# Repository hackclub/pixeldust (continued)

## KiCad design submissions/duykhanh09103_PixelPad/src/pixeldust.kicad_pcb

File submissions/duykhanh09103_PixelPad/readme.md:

---
name: "Khanh Duy Thanh Vo (my actually name in like gov document is Vo Thanh Khanh Duy because of last name fist name)"
slack_id: "U081GA0TAPR"
github_handle: "@duykhanh09103"
tutorial: none
wokwi: https://wokwi.com/projects/428194723515552769
---

# PixelPad

Replace the wokwi link below with yours

Wokwi link: https://wokwi.com/projects/428194723515552769

<!-- Uncomment the line below if you need a soldering iron -->
<!-- ⚠️ I would like to [reason for iron], so I would need a soldering iron. -->

<!-- Example: -->

| Comment           | Footprint                                      | Quantity | LCSC     | Cost   |
|-------------------|------------------------------------------------|----------|----------|--------|
| 100nF             | CL10B224KA8NNNC                                | 1        | C21120   | 0.0682$|
| WS2812B           | SK6812MINI-EA                                  | 9        | C5378731 |        |
| XIAO-RP2040-DIP   | XIAO-RP2040-DIP                                | 1        |          |        |
| Cherry MX         | SW_Cherry_MX_1.00u_PCB                         | 3        |          | 1.3$ for 3 |
| Hall Effect Sensor| GH39FKSW                                       | 3        | C266230  | $0.1439|

Tell us a little bit about your design process. What were some challenges? What helped?

originally i wanna design like  a 10x10 pixel board so i can display like image,qr,.. on it but i shuddenly have some idea about making  a keypad!
there was not a lot of challenge cuz @tobycm helped me a lot with kicad!(hes the goat 🗣). 

Some images of your design (make sure to include both the PCB and Schematic!):

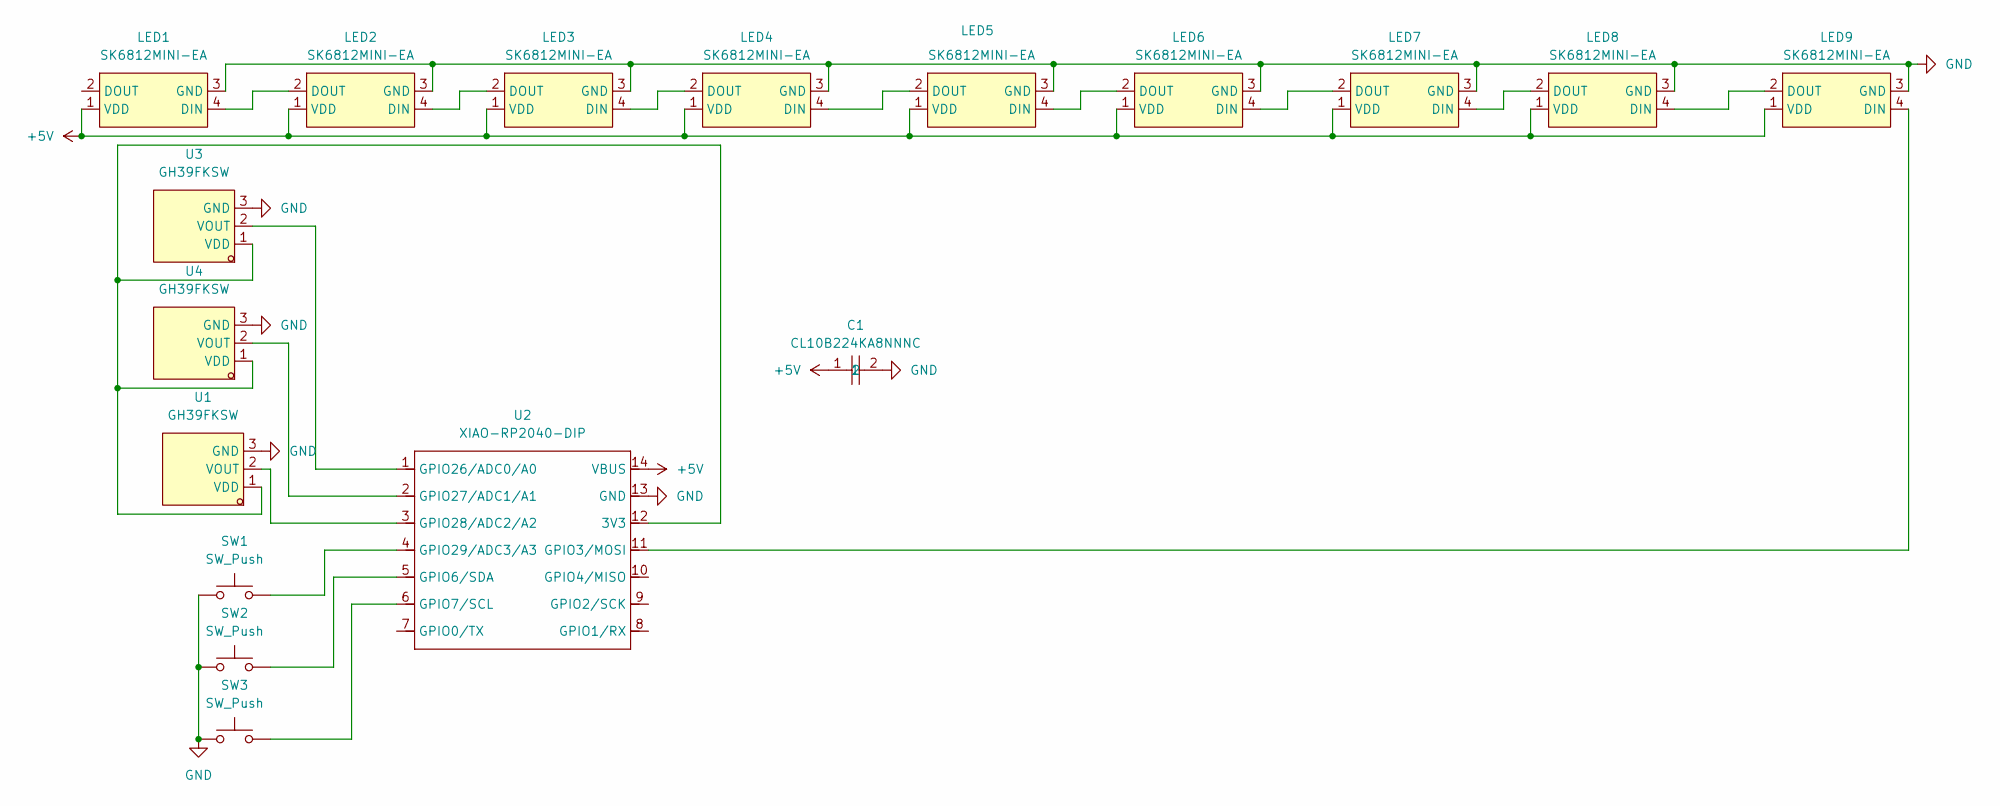
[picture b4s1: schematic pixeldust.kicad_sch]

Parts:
C1: CL10B224KA8NNNC; C0603; LCSC Part C21120
LED1, LED2, LED3, LED4, LED5, LED6, LED7, LED8, LED9: SK6812MINI-EA; LED-SMD_4P-L3.2-W2.8_SK6812MINI-EA; LCSC Part C5378731
SW1, SW2, SW3: SW_Push; SW_Cherry_MX_1.00u_PCB
U1, U3, U4: GH39FKSW; SOT-23-3_L2.9-W1.3-P1.90-LS2.4-BR; LCSC Part C266230
U2: XIAO-RP2040-DIP

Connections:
+5V: C1.1, LED1.1 (VDD), LED2.1 (VDD), LED3.1 (VDD), LED4.1 (VDD), LED5.1 (VDD), LED6.1 (VDD), LED7.1 (VDD), LED8.1 (VDD), LED9.1 (VDD), U2.14 (VBUS)
GND: C1.2, LED1.3 (GND), LED2.3 (GND), LED3.3 (GND), LED4.3 (GND), LED5.3 (GND), LED6.3 (GND), LED7.3 (GND), LED8.3 (GND), LED9.3 (GND), SW1.1, SW2.1, SW3.1, U1.3 (GND), U2.13 (GND), U3.3 (GND), U4.3 (GND)
unnamed: LED1.4 (DIN), LED2.2 (DOUT)
unnamed: LED2.4 (DIN), LED3.2 (DOUT)
unnamed: LED3.4 (DIN), LED4.2 (DOUT)
unnamed: LED4.4 (DIN), LED5.2 (DOUT)
unnamed: LED5.4 (DIN), LED6.2 (DOUT)
unnamed: LED6.4 (DIN), LED7.2 (DOUT)
unnamed: LED7.4 (DIN), LED8.2 (DOUT)
unnamed: LED8.4 (DIN), LED9.2 (DOUT)
unnamed: LED9.4 (DIN), U2.11 (GPIO3/MOSI)
unnamed: U1.1 (VDD), U2.12 (3V3), U3.1 (VDD), U4.1 (VDD)
unnamed: U1.2 (VOUT), U2.3 (GPIO28/ADC2/A2)
unnamed: SW2.2, U2.5 (GPIO6/SDA)
unnamed: SW3.2, U2.6 (GPIO7/SCL)
unnamed: U2.1 (GPIO26/ADC0/A0), U3.2 (VOUT)
unnamed: U2.2 (GPIO27/ADC1/A1), U4.2 (VOUT)
unnamed: SW1.2, U2.4 (GPIO29/ADC3/A3)

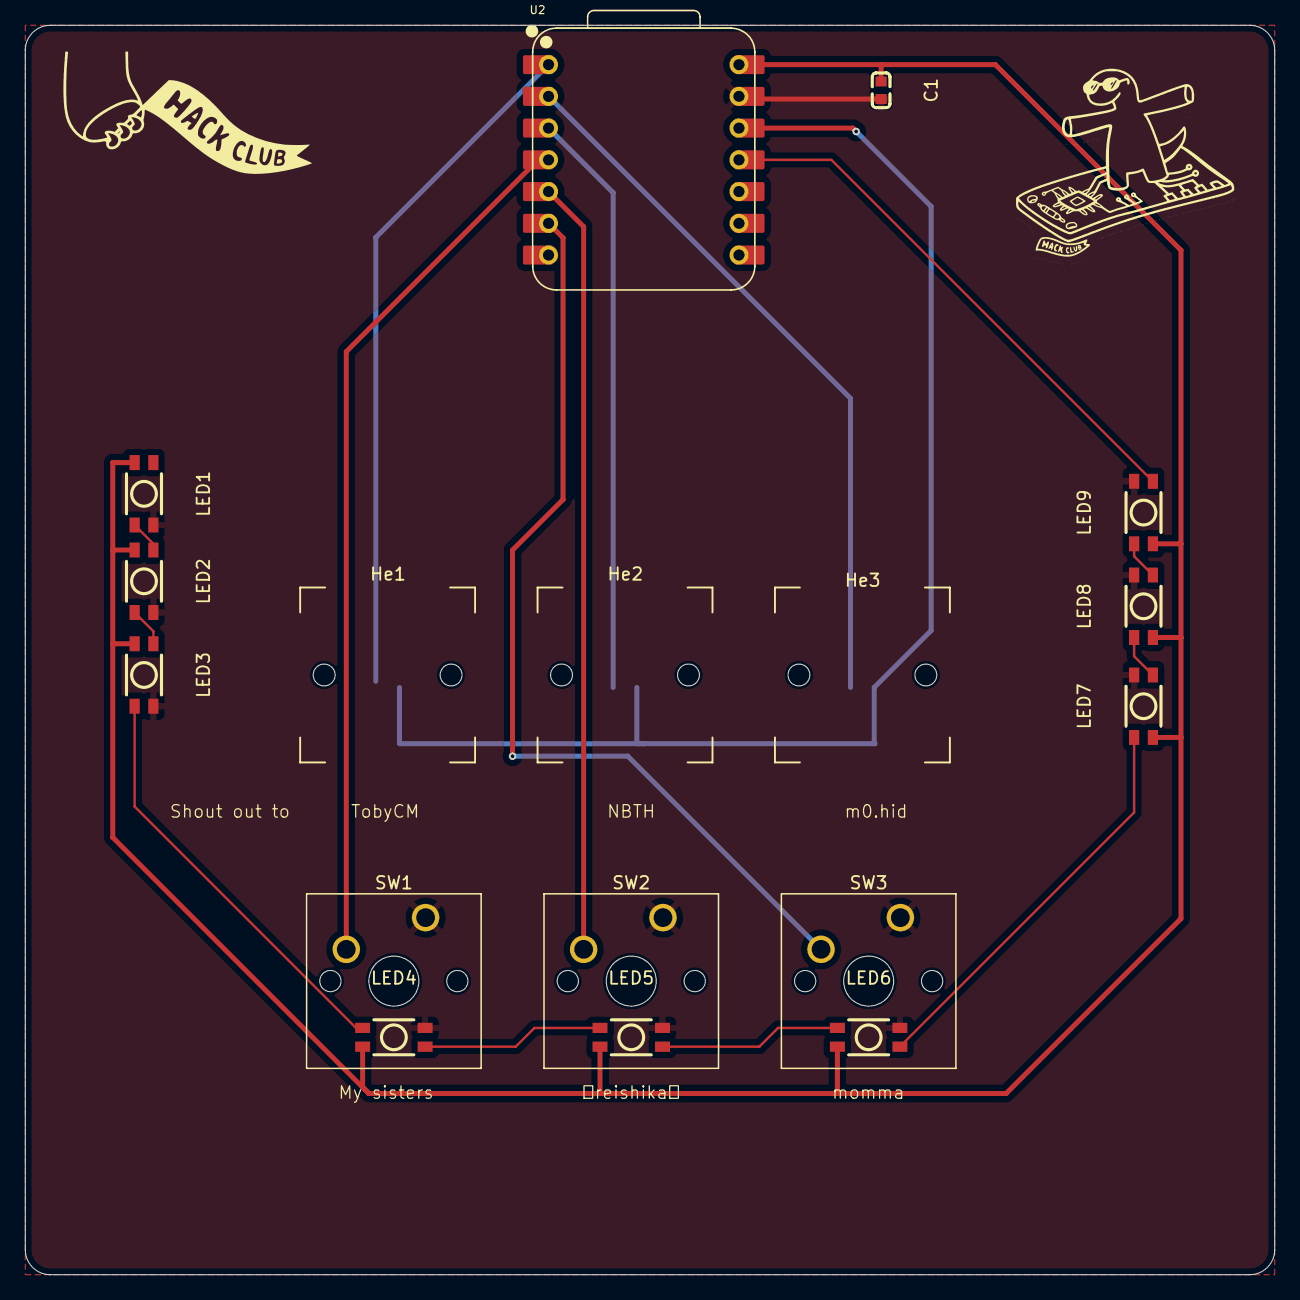
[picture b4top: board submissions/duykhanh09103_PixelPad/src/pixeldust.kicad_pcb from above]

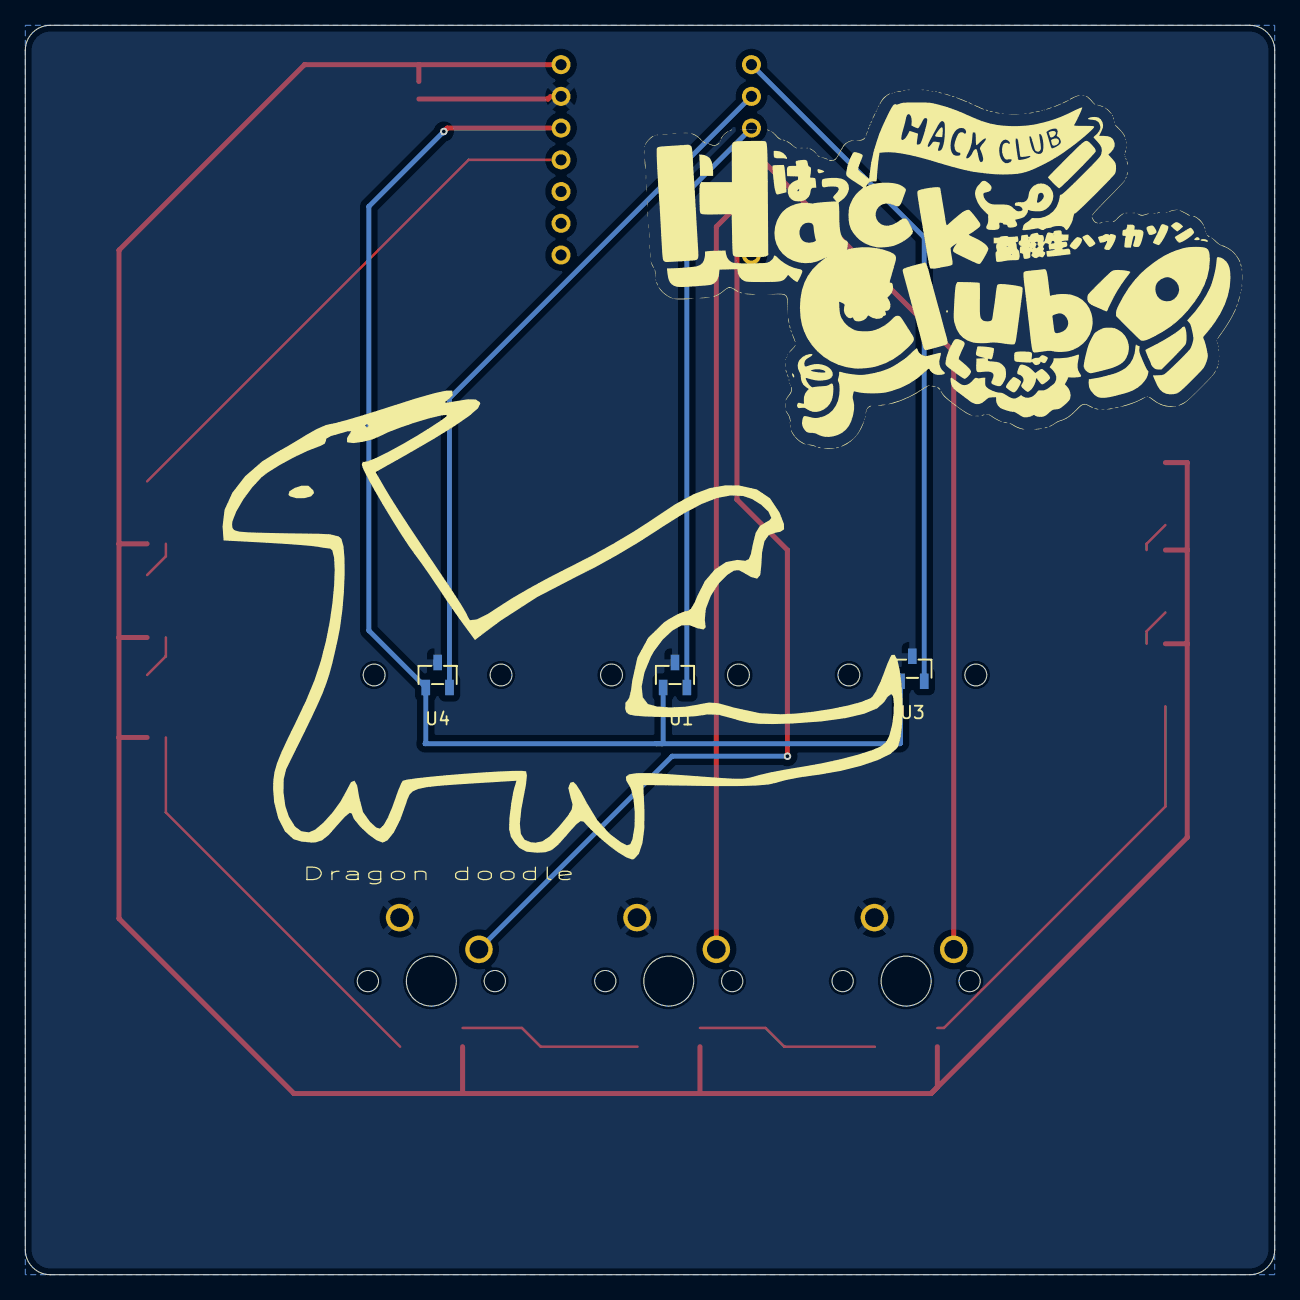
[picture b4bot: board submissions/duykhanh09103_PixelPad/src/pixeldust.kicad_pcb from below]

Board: 2 copper layers, 100.0 x 100.0 mm, 17 parts (3 on the bottom side), 18 nets.

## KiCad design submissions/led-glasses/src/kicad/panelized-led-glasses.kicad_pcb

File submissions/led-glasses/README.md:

---
name: "Mircea-Sebastian Turtureanu"
slack_id: "U07V1G4396G"
github_handle: "@turtureanu"
tutorial: https://pixeldust.hackclub.com/guidelines
wokwi: https://wokwi.com/projects/428024875914576897
---

# LED Glasses

Wokwi link: [https://wokwi.com/projects/428024875914576897](https://wokwi.com/projects/428024875914576897)

<!-- Describe your board in 2-3 sentences. What are you making? What will it do? Please add a lot of pictures here!! -->

LED glasses, which you can put on, configure and see through! They look kind of cool, shouldn't be that uncomfortable to wear.
There is a button on the side, which can be used to toggle between different animations. In the future I plan on implementing a website that can be used to change the animation and modify each pixel individually. The website could be used by the user by connecting to the XIAO ESP32-S3 (in WAP mode).

This board is a panelized PCB that has 3 parts.

A simplified BOM table:

> !WARNING!
> The prices in the table are the total amount (not per unit)!

| Comment           | Footprint                                      | Quantity | LCSC     | Cost   |
|-------------------|------------------------------------------------|----------|----------|--------|
| 100uF             | Capacitor_C1206_SMD                            | 1        | C15008   | 0.0682$|
| 4.7nF             | Capacitor_C1206_SMD                            | 3        | C9192    | 0.0315$|
| SK6812MINI-012    | LED-SMD_4P-L3.7-W3.5-P1.75-BR-SK6812MINI       | 62       | C2886570 | 5.7350$|
| XIAO ESP32-S3     | XIAO ESP32-S3                                  | 1        |          |        |  
| Tactile switch    | SW-SMD_L3.9-W3.0-P4.45                         | 1        | C720477  | 0.0394$|

The design process wasn't that bad, the challenge I faced the most were repetitive tasks I couldn't automate, the wiring of the PCB was also somewhat tricky because of the tight space and the amount of connections. But the hardest thing was getting the EasyEDA 3D models for the PCB.

## License

My code and design are licensed under the GPLv3 license available at: https://www.gnu.org/licenses/gpl-3.0.en.html

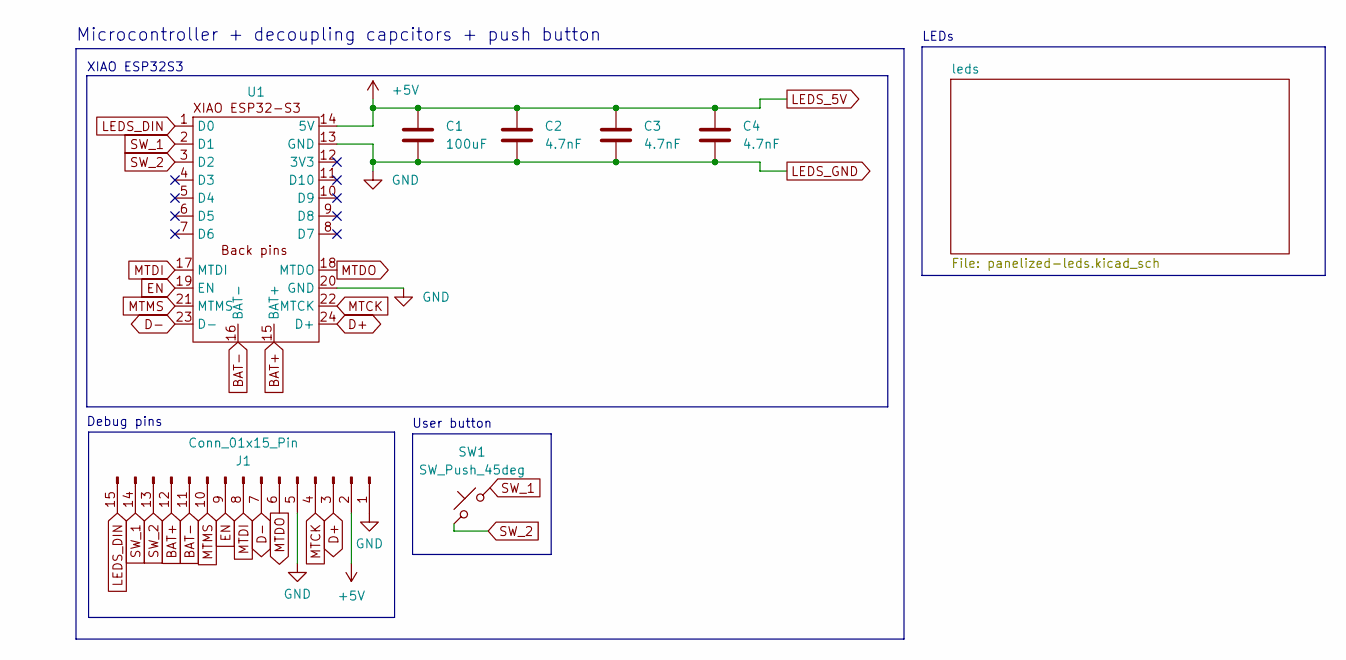
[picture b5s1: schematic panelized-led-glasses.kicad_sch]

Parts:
C1: 100uF; Capacitor_C1206_SMD
C2, C3, C4: 4.7nF; Capacitor_C1206_SMD
J1: Conn_01x15_Pin; PinSocket_1x15_P2.54mm_Vertical
SW1: SW_Push_45deg; SW-SMD_L3.9-W3.0-P4.45
U1: XIAO-ESP32S3-SMD

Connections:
BAT+: J1.12, U1.15 (BAT+)
BAT-: J1.11, U1.16 (BAT-)
D+: J1.3, U1.24 (D+)
D-: J1.7, U1.23 (D-)
EN: J1.9, U1.19 (EN)
LEDS_5V: C1.1, C2.1, C3.1, C4.1, J1.2, U1.14 (5V); also elsewhere on the board
LEDS_DIN: J1.15, U1.1 (D0); also elsewhere on the board
LEDS_GND: C1.2, C2.2, C3.2, C4.2, J1.1, J1.5, U1.13 (GND), U1.20 (GND); also elsewhere on the board
MTCK: J1.4, U1.22 (MTCK)
MTDI: J1.8, U1.17 (MTDI)
MTDO: J1.6, U1.18 (MTDO)
MTMS: J1.10, U1.21 (MTMS)
SW_1: J1.14, SW1.1, U1.2 (D1)
SW_2: J1.13, SW1.2, U1.3 (D2)

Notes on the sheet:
Microcontroller + decoupling capcitors + push button
User button
XIAO ESP32S3
Debug pins
LEDs

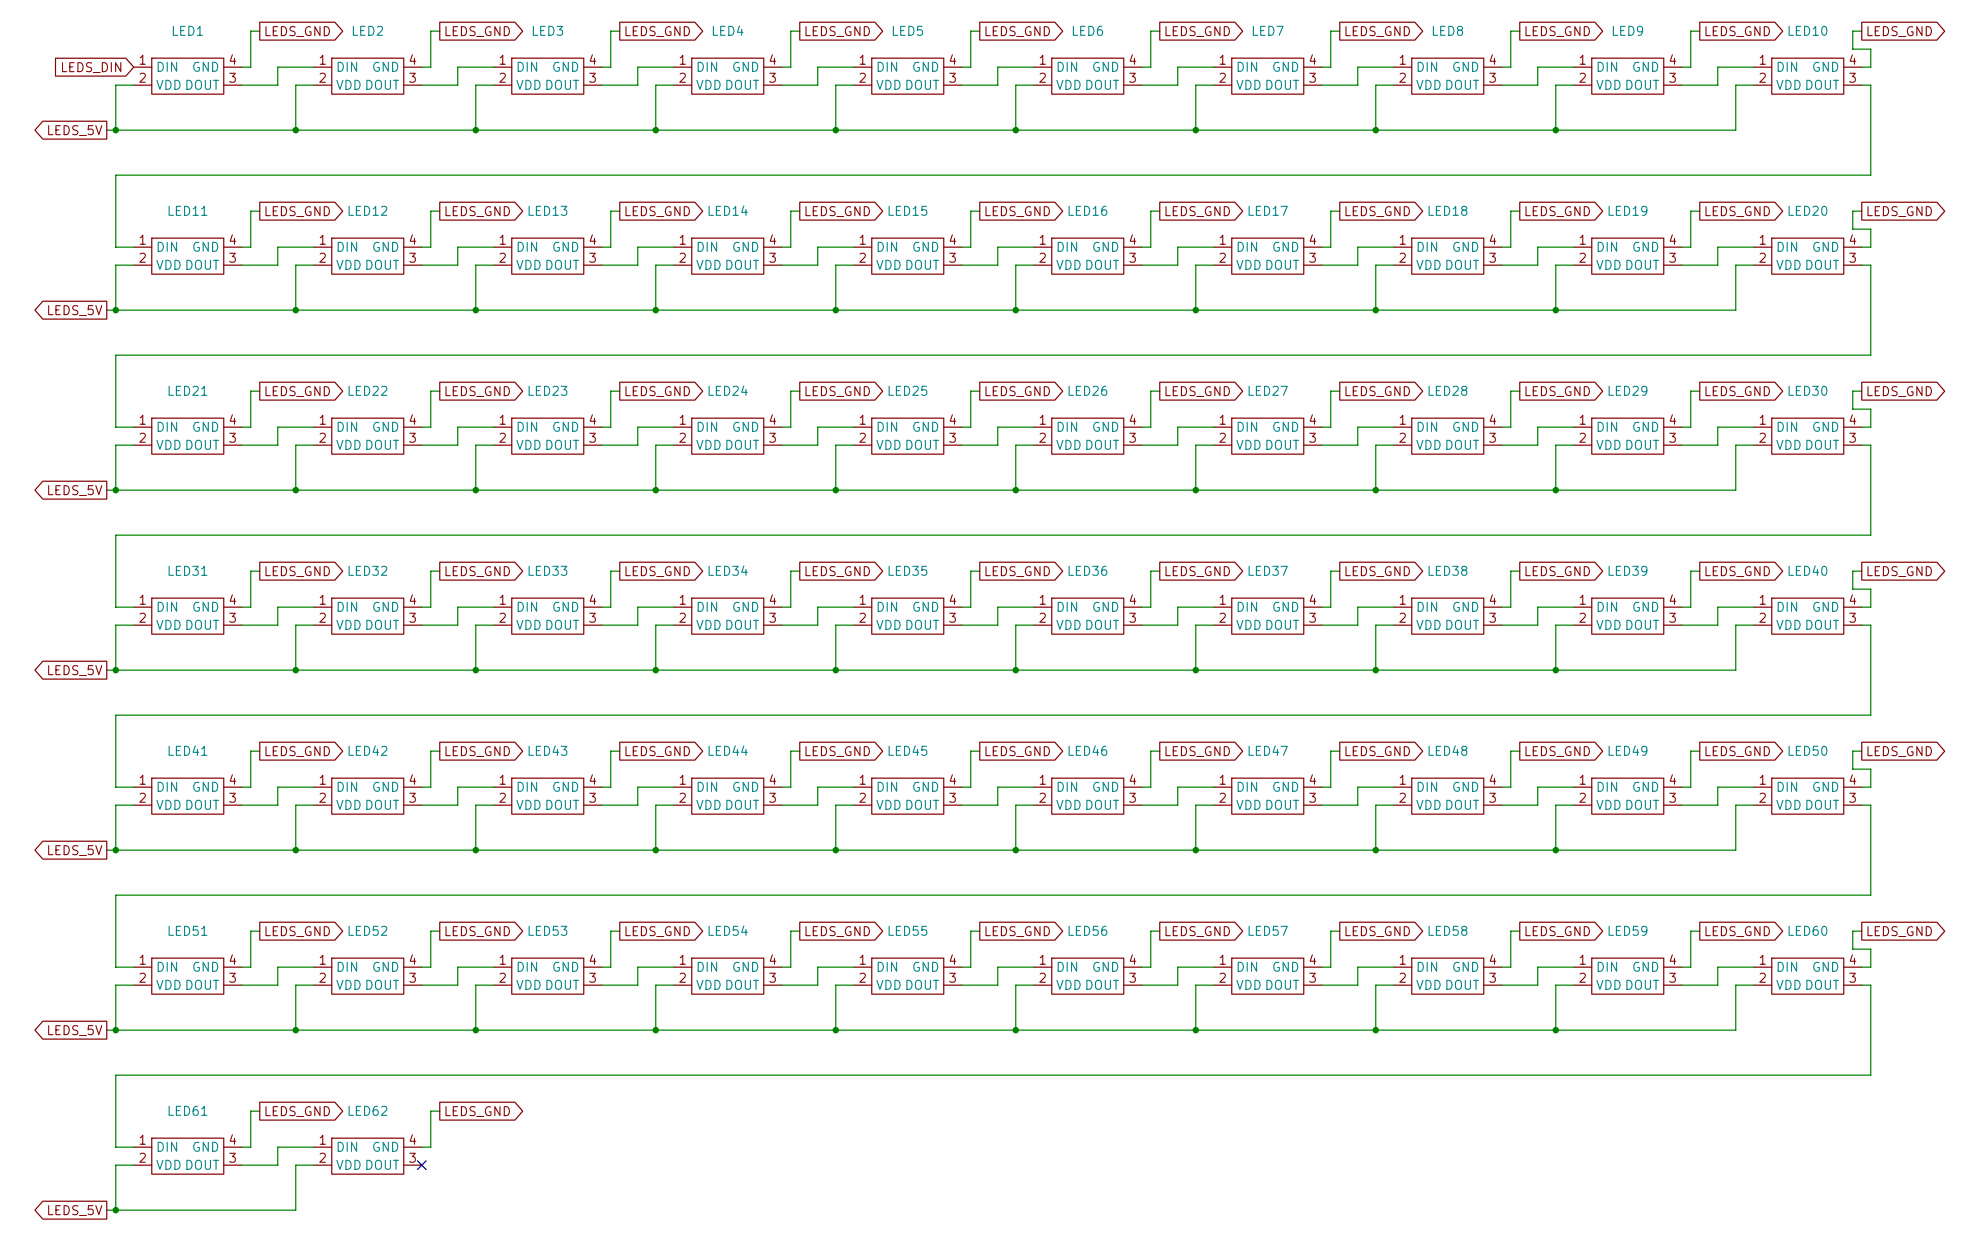
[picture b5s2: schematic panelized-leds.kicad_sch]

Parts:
LED1, LED2, LED3, LED4, LED5, LED6, LED7, LED8, LED9, LED10, LED11, LED12, LED13, LED14, LED15, LED16, LED17, LED18, LED19, LED20, LED21, LED22, LED23, LED24, LED25, LED26, LED27, LED28, LED29, LED30, LED31, LED32, LED33, LED34, LED35, LED36, LED37, LED38, LED39, LED40, LED41, LED42, LED43, LED44, LED45, LED46, LED47, LED48, LED49, LED50, LED51, LED52, LED53, LED54, LED55, LED56, LED57, LED58, LED59, LED60, LED61, LED62: LED-SMD_4P-L3.7-W3.5-P1.75-BR-SK6812MINI

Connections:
LEDS_5V: LED1.2 (VDD), LED2.2 (VDD), LED3.2 (VDD), LED4.2 (VDD), LED5.2 (VDD), LED6.2 (VDD), LED7.2 (VDD), LED8.2 (VDD), LED9.2 (VDD), LED10.2 (VDD), LED11.2 (VDD), LED12.2 (VDD), LED13.2 (VDD), LED14.2 (VDD), LED15.2 (VDD), LED16.2 (VDD), LED17.2 (VDD), LED18.2 (VDD), LED19.2 (VDD), LED20.2 (VDD), LED21.2 (VDD), LED22.2 (VDD), LED23.2 (VDD), LED24.2 (VDD), LED25.2 (VDD), LED26.2 (VDD), LED27.2 (VDD), LED28.2 (VDD), LED29.2 (VDD), LED30.2 (VDD), LED31.2 (VDD), LED32.2 (VDD), LED33.2 (VDD), LED34.2 (VDD), LED35.2 (VDD), LED36.2 (VDD), LED37.2 (VDD), LED38.2 (VDD), LED39.2 (VDD), LED40.2 (VDD), LED41.2 (VDD), LED42.2 (VDD), LED43.2 (VDD), LED44.2 (VDD), LED45.2 (VDD), LED46.2 (VDD), LED47.2 (VDD), LED48.2 (VDD), LED49.2 (VDD), LED50.2 (VDD), LED51.2 (VDD), LED52.2 (VDD), LED53.2 (VDD), LED54.2 (VDD), LED55.2 (VDD), LED56.2 (VDD), LED57.2 (VDD), LED58.2 (VDD), LED59.2 (VDD), LED60.2 (VDD), LED61.2 (VDD), LED62.2 (VDD); also elsewhere on the board
LEDS_DIN: LED1.1 (DIN); also elsewhere on the board
LEDS_GND: LED1.4 (GND), LED2.4 (GND), LED3.4 (GND), LED4.4 (GND), LED5.4 (GND), LED6.4 (GND), LED7.4 (GND), LED8.4 (GND), LED9.4 (GND), LED10.4 (GND), LED11.4 (GND), LED12.4 (GND), LED13.4 (GND), LED14.4 (GND), LED15.4 (GND), LED16.4 (GND), LED17.4 (GND), LED18.4 (GND), LED19.4 (GND), LED20.4 (GND), LED21.4 (GND), LED22.4 (GND), LED23.4 (GND), LED24.4 (GND), LED25.4 (GND), LED26.4 (GND), LED27.4 (GND), LED28.4 (GND), LED29.4 (GND), LED30.4 (GND), LED31.4 (GND), LED32.4 (GND), LED33.4 (GND), LED34.4 (GND), LED35.4 (GND), LED36.4 (GND), LED37.4 (GND), LED38.4 (GND), LED39.4 (GND), LED40.4 (GND), LED41.4 (GND), LED42.4 (GND), LED43.4 (GND), LED44.4 (GND), LED45.4 (GND), LED46.4 (GND), LED47.4 (GND), LED48.4 (GND), LED49.4 (GND), LED50.4 (GND), LED51.4 (GND), LED52.4 (GND), LED53.4 (GND), LED54.4 (GND), LED55.4 (GND), LED56.4 (GND), LED57.4 (GND), LED58.4 (GND), LED59.4 (GND), LED60.4 (GND), LED61.4 (GND), LED62.4 (GND); also elsewhere on the board
unnamed: LED1.3 (DOUT), LED2.1 (DIN)
unnamed: LED2.3 (DOUT), LED3.1 (DIN)
unnamed: LED3.3 (DOUT), LED4.1 (DIN)
unnamed: LED4.3 (DOUT), LED5.1 (DIN)
unnamed: LED5.3 (DOUT), LED6.1 (DIN)
unnamed: LED6.3 (DOUT), LED7.1 (DIN)
unnamed: LED7.3 (DOUT), LED8.1 (DIN)
unnamed: LED8.3 (DOUT), LED9.1 (DIN)
unnamed: LED9.3 (DOUT), LED10.1 (DIN)
unnamed: LED10.3 (DOUT), LED11.1 (DIN)
unnamed: LED11.3 (DOUT), LED12.1 (DIN)
unnamed: LED12.3 (DOUT), LED13.1 (DIN)
unnamed: LED13.3 (DOUT), LED14.1 (DIN)
unnamed: LED14.3 (DOUT), LED15.1 (DIN)
unnamed: LED15.3 (DOUT), LED16.1 (DIN)
unnamed: LED16.3 (DOUT), LED17.1 (DIN)
unnamed: LED17.3 (DOUT), LED18.1 (DIN)
unnamed: LED18.3 (DOUT), LED19.1 (DIN)
unnamed: LED19.3 (DOUT), LED20.1 (DIN)
unnamed: LED20.3 (DOUT), LED21.1 (DIN)
unnamed: LED21.3 (DOUT), LED22.1 (DIN)
unnamed: LED22.3 (DOUT), LED23.1 (DIN)
unnamed: LED23.3 (DOUT), LED24.1 (DIN)
unnamed: LED24.3 (DOUT), LED25.1 (DIN)
unnamed: LED25.3 (DOUT), LED26.1 (DIN)
unnamed: LED26.3 (DOUT), LED27.1 (DIN)
unnamed: LED27.3 (DOUT), LED28.1 (DIN)
unnamed: LED28.3 (DOUT), LED29.1 (DIN)
unnamed: LED29.3 (DOUT), LED30.1 (DIN)
unnamed: LED30.3 (DOUT), LED31.1 (DIN)
unnamed: LED31.3 (DOUT), LED32.1 (DIN)
unnamed: LED32.3 (DOUT), LED33.1 (DIN)
unnamed: LED33.3 (DOUT), LED34.1 (DIN)
unnamed: LED34.3 (DOUT), LED35.1 (DIN)
unnamed: LED35.3 (DOUT), LED36.1 (DIN)
unnamed: LED36.3 (DOUT), LED37.1 (DIN)
unnamed: LED37.3 (DOUT), LED38.1 (DIN)
unnamed: LED38.3 (DOUT), LED39.1 (DIN)
unnamed: LED39.3 (DOUT), LED40.1 (DIN)
unnamed: LED40.3 (DOUT), LED41.1 (DIN)
unnamed: LED41.3 (DOUT), LED42.1 (DIN)
unnamed: LED42.3 (DOUT), LED43.1 (DIN)
unnamed: LED43.3 (DOUT), LED44.1 (DIN)
unnamed: LED44.3 (DOUT), LED45.1 (DIN)
unnamed: LED45.3 (DOUT), LED46.1 (DIN)
unnamed: LED46.3 (DOUT), LED47.1 (DIN)
unnamed: LED47.3 (DOUT), LED48.1 (DIN)
unnamed: LED48.3 (DOUT), LED49.1 (DIN)
unnamed: LED49.3 (DOUT), LED50.1 (DIN)
unnamed: LED50.3 (DOUT), LED51.1 (DIN)
unnamed: LED51.3 (DOUT), LED52.1 (DIN)
unnamed: LED52.3 (DOUT), LED53.1 (DIN)
unnamed: LED53.3 (DOUT), LED54.1 (DIN)
unnamed: LED54.3 (DOUT), LED55.1 (DIN)
unnamed: LED55.3 (DOUT), LED56.1 (DIN)
unnamed: LED56.3 (DOUT), LED57.1 (DIN)
unnamed: LED57.3 (DOUT), LED58.1 (DIN)
unnamed: LED58.3 (DOUT), LED59.1 (DIN)
unnamed: LED59.3 (DOUT), LED60.1 (DIN)
unnamed: LED60.3 (DOUT), LED61.1 (DIN)
unnamed: LED61.3 (DOUT), LED62.1 (DIN)

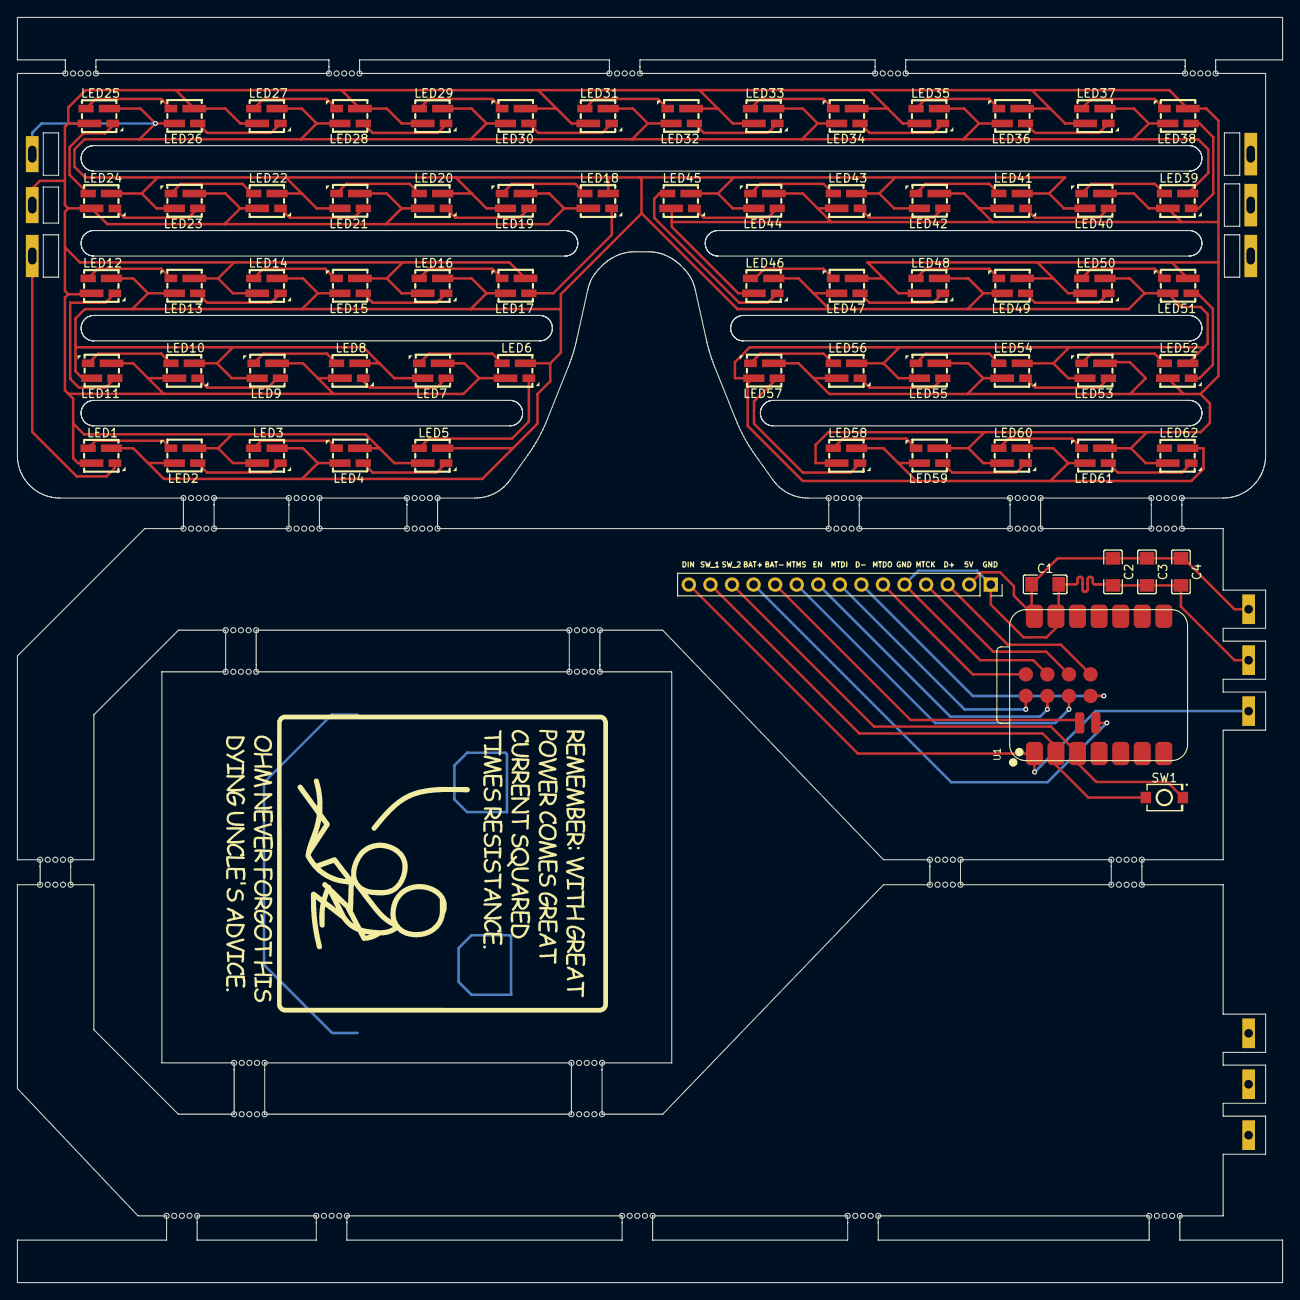
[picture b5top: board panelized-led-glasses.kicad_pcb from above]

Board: 2 copper layers, 149.0 x 149.0 mm, 184 parts (0 on the bottom side), 75 nets.

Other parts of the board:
KiKit_MB_1_1, KiKit_MB_1_2, KiKit_MB_1_3, KiKit_MB_1_4, KiKit_MB_1_5, KiKit_MB_2_1, KiKit_MB_2_2, KiKit_MB_2_3, KiKit_MB_2_4, KiKit_MB_2_5, KiKit_MB_3_1, KiKit_MB_3_2, KiKit_MB_3_3, KiKit_MB_3_4, KiKit_MB_3_5, KiKit_MB_4_1, KiKit_MB_4_2, KiKit_MB_4_3, KiKit_MB_4_4, KiKit_MB_4_5, KiKit_MB_5_1, KiKit_MB_5_2, KiKit_MB_5_3, KiKit_MB_5_4, KiKit_MB_5_5, KiKit_MB_6_1, KiKit_MB_6_2, KiKit_MB_6_3, KiKit_MB_6_4, KiKit_MB_6_5, KiKit_MB_7_1, KiKit_MB_7_2, KiKit_MB_7_3, KiKit_MB_7_4, KiKit_MB_7_5, KiKit_MB_8_1, KiKit_MB_8_2, KiKit_MB_8_3, KiKit_MB_8_4, KiKit_MB_8_5, KiKit_MB_9_1, KiKit_MB_9_2, KiKit_MB_9_3, KiKit_MB_9_4, KiKit_MB_9_5, KiKit_MB_10_1, KiKit_MB_10_2, KiKit_MB_10_3, KiKit_MB_10_4, KiKit_MB_10_5, KiKit_MB_11_1, KiKit_MB_11_2, KiKit_MB_11_3, KiKit_MB_11_4, KiKit_MB_11_5, KiKit_MB_12_1, KiKit_MB_12_2, KiKit_MB_12_3, KiKit_MB_12_4, KiKit_MB_12_5, KiKit_MB_13_1, KiKit_MB_13_2, KiKit_MB_13_3, KiKit_MB_13_4, KiKit_MB_13_5, KiKit_MB_14_1, KiKit_MB_14_2, KiKit_MB_14_3, KiKit_MB_14_4, KiKit_MB_14_5, KiKit_MB_15_1, KiKit_MB_15_2, KiKit_MB_15_3, KiKit_MB_15_4, KiKit_MB_15_5, KiKit_MB_16_1, KiKit_MB_16_2, KiKit_MB_16_3, KiKit_MB_16_4, KiKit_MB_16_5, KiKit_MB_17_1, KiKit_MB_17_2, KiKit_MB_17_3, KiKit_MB_17_4, KiKit_MB_17_5, KiKit_MB_18_1, KiKit_MB_18_2, KiKit_MB_18_3, KiKit_MB_18_4, KiKit_MB_18_5, KiKit_MB_19_1, KiKit_MB_19_2, KiKit_MB_19_3, KiKit_MB_19_4, KiKit_MB_19_5, KiKit_MB_20_1, KiKit_MB_20_2, KiKit_MB_20_3, KiKit_MB_20_4, KiKit_MB_20_5, KiKit_MB_21_1, KiKit_MB_21_2, KiKit_MB_21_3, KiKit_MB_21_4, KiKit_MB_21_5, KiKit_MB_22_1, KiKit_MB_22_2, KiKit_MB_22_3, KiKit_MB_22_4, KiKit_MB_22_5, KiKit_MB_23_1, KiKit_MB_23_2, KiKit_MB_23_3, KiKit_MB_23_4, KiKit_MB_23_5: NPTH
